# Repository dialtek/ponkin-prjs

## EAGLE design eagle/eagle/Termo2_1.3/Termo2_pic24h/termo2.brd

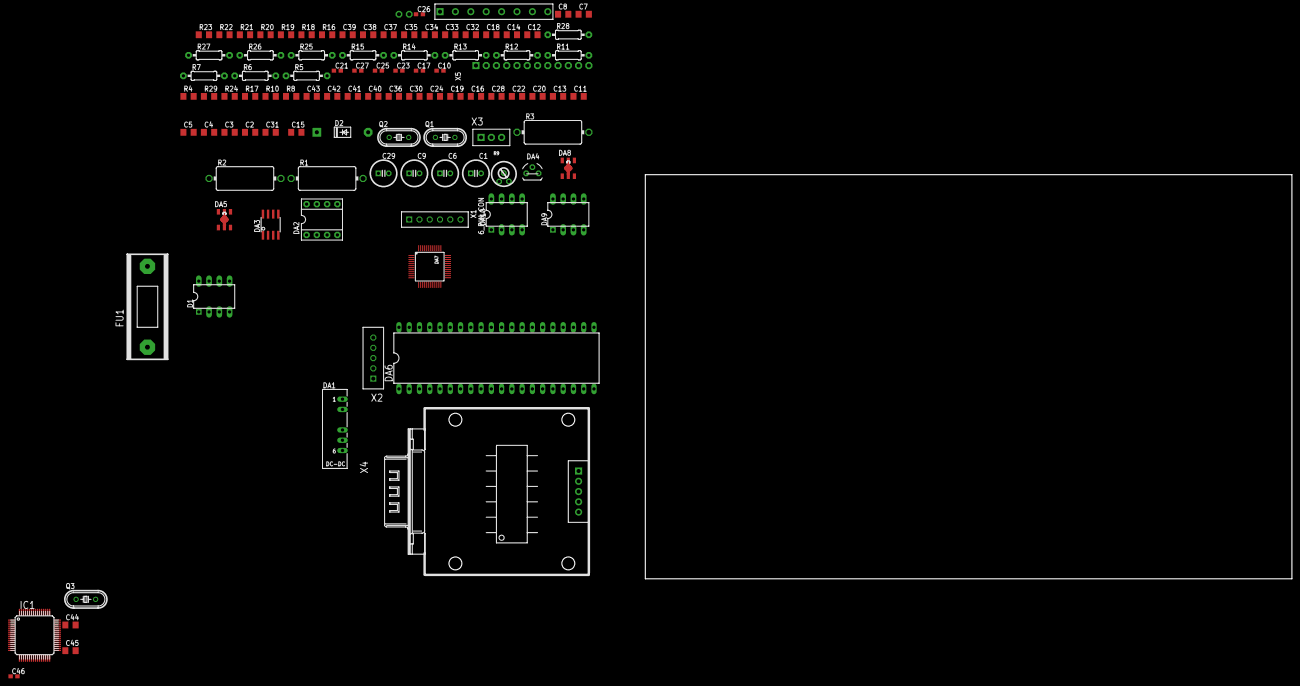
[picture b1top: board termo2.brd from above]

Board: 2 copper layers, 160.0 x 100.0 mm, 100 parts (0 on the bottom side), 77 nets, no tracks yet.

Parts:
8_PIN_: 8_PIN_CON
C1, C6, C9, C29: C100MILX6X12
C2, C3, C4, C5, C11, C13, C20, C22, C28: 0.1u; C0805D
C7, C8, C12, C14, C18, C32, C33, C34, C35, C37, C38, C39: C0805D
C10, C17, C23, C25, C27, C46: 0.1u; C0603
C15, C31: 0.01u; C0805D
C16, C30: 1u; C0805D
C19, C24, C44, C45: 12p; C0805D
C21: 1n; C0603
C26: C0603
C36: 1n; C0805D
C40, C41, C42, C43: 0.1; C0805D
D1: 6N137; DIL08
D2: 1N5061; DO41-10
DA1: NMA
DA2: INA128P; DIL08
DA3: OPA340U; SO08
DA4: DS1811; TO92-60
DA5, DA8: NJM2880; SOT89-5
DA6: PIC18F4320_40; DIL40
DA7: ADS1216ADS1216; ADS1216_PAC
DA9, DA10: CNY74-H; CNY_DIP8
FU1: FUSE5X20
IC1: PIC24HJ64GP506; TQFP64-10X10
P1, P2: 1_PIN_CON
Q1, Q2, Q3: HC49/S
R1, R2: 100k; V235/17
R3: 50k; V235/17
R4, R24: 10k; R0805D
R5, R25, R26, R27, R28: 330; 0207/10
R6, R7: 1k; 0207/10
R8, R10, R29: 22R; R0805D
R9: RTRIM3329H
R11: 100k; 0207/10
R12, R13, R14, R15: 4k7; 0207/10
R16, R18, R19, R20, R21, R22, R23: R0805D
R17: 1k; R0805D
X1: 6_PIN_CON; 6_IN_PINS
X2: PLC-5PIN
X3: PLC-3PIN
X4: KM_RS_232
X5: WINSTAR16X4_12

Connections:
!MCLR_MC: IC1.7, R4.P$1, X3.P$2
+5V: C1.PLUS, C2.1, C4.2, C5.1, C11.2, C18.2, C20.1, C22.2, C29.PLUS, C30.1, D1.7, D1.8, DA1.1, DA3.7, DA4.2, DA6.11, DA6.32, DA8.4, R4.P$2, R6.2, R9.2, R12.2, R13.2, R14.2, R15.2, X1.P$5, X2.P$2, X4.5, X5.P$2
+5V_AVDD: C10.2, C16.1, C23.2, C25.1, C26.2, C27.1, DA5.4, DA7.1, DA7.13, DA7.23, DA7.27, DA7.31
+6V: C13.2, C28.2, D2.C, DA5.1, DA5.5, DA8.1, DA8.5, FU1.P$2, R7.1
AINCOM: DA7.11, R11.1
DB4: DA6.27, X5.P$7
DB5: DA6.28, X5.P$8
DB6: DA6.29, X5.P$9
DB7: DA6.30, X5.P$10
DRDY: DA6.5, DA7.32
DSYNC: DA6.6, DA7.29
D_IN: DA7.35, R10.P$2
D_OUT: DA7.36, R8.P$2
E: DA6.19, X5.P$6
IN1.1: C36.1, C40.1, DA7.3, R17.P$1
IN1.2: C32.1, C40.2, DA7.4, R18.P$1
IN2.1: C37.1, C41.1, DA7.5, R19.P$1
IN2.2: C33.1, C41.2, DA7.6, R20.P$1
IN3.1: C38.1, C42.1, DA7.7, R23.P$1
IN3.2: C34.1, C42.2, DA7.8, R16.P$1
IN4.1: C39.1, C43.1, DA7.9, R21.P$1
IN4.2: C35.1, C43.2, DA7.10, R22.P$1
INA_OUT: DA3.3, R3.1
K2: R26.2, X1.P$2
K3: R27.1, X1.P$3
K4: R28.2, X1.P$4
KN1,PGD: DA9.7, IC1.18, R12.1, X2.P$4
KN2,PGC: DA9.6, IC1.17, R13.1, X2.P$5
KN3: DA6.38, DA10.7, R14.1
KN4: DA6.37, DA10.6, R15.1
MCLR: X2.P$1, X3.P$1
unnamed: C19.2, DA6.13, Q2.1
unnamed: C24.2, DA6.14, Q2.2
unnamed: DA9.4, R26.1
unnamed: C31.1, DA8.3
unnamed: D1.6, DA6.35, R6.1
unnamed: DA6.18, R29.P$2
unnamed: C21.2, DA7.14
unnamed: DA4.1, X3.P$3
unnamed: DA6.24, R10.P$1
unnamed: C14.2, DA7.25, Q1.2
unnamed: C12.2, DA7.26, Q1.1
unnamed: DA6.23, R8.P$1
unnamed: 8_PIN_.P$6, R16.P$2
unnamed: 8_PIN_.P$1, R17.P$2
unnamed: 8_PIN_.P$2, R18.P$2
unnamed: 8_PIN_.P$7, R21.P$2
unnamed: DA10.1, R27.2
unnamed: 8_PIN_.P$8, R22.P$2, R24.P$1
unnamed: DA10.4, R28.1
unnamed: R7.2, X5.P$11
unnamed: 8_PIN_.P$5, R23.P$2
unnamed: C6.PLUS, C8.1, DA1.6, DA2.7
unnamed: 8_PIN_.P$3, R19.P$2
unnamed: 8_PIN_.P$4, R20.P$2
unnamed: DA2.5, DA3.2, DA3.6
unnamed: DA2.6, R1.2
unnamed: C7.1, C9.MINUS, DA1.4, DA2.4
unnamed: R1.1, R2.2
unnamed: R2.1, R3.2
unnamed: C15.1, DA5.3
unnamed: D1.2, R5.1
unnamed: D1.3, P1.P$1
unnamed: P2.P$1, R5.2
OSC1: C44.2, IC1.39, Q3.1
OSC2: C45.2, IC1.40, Q3.2
PE: C1.MINUS, C2.2, C3.2, C4.1, C5.2, C6.MINUS, C7.2, C8.2, C9.PLUS, C10.1, C11.1, C12.1, C13.1, C14.1, C15.2, C16.2, C17.2, C18.1, C19.1, C20.2, C21.1, C22.1, C23.1, C24.1, C25.2, C26.1, C27.2, C28.1, C29.MINUS, C30.2, C31.2, C32.2, C33.2, C34.2, C35.2, C36.2, C37.2, C38.2, C39.2, C44.1, C45.1, C46.1, C46.2, D1.5, D2.A, DA1.2, DA1.5, DA2.2, DA3.4, DA4.3, DA5.2, DA5.21, DA6.12, DA6.31, DA7.2, DA7.12, DA7.18, DA7.19, DA7.20, DA7.21, DA7.22, DA7.28, DA7.30, DA7.45, DA7.48, DA8.2, DA8.21, DA9.2, DA9.3, DA9.5, DA9.8, DA10.2, DA10.3, DA10.5, DA10.8, IC1.38, IC1.41, R9.1, R11.2, R24.P$2, X1.P$6, X2.P$3, X4.1, X5.P$1, X5.P$12
R15: DA9.1, R25.2
REF: C3.1, C17.1, DA2.3, DA7.46, DA7.47
RESET: DA6.7, DA7.24
RS: DA6.21, X5.P$4
RW: DA6.22, X5.P$5
SCLK: DA7.34, R29.P$1
TX_EN: DA6.20, X4.4
V0CON: R9.3, X5.P$3
VDD: FU1.P$1, IC1.10, IC1.26, IC1.57
VSS: IC1.9, IC1.25

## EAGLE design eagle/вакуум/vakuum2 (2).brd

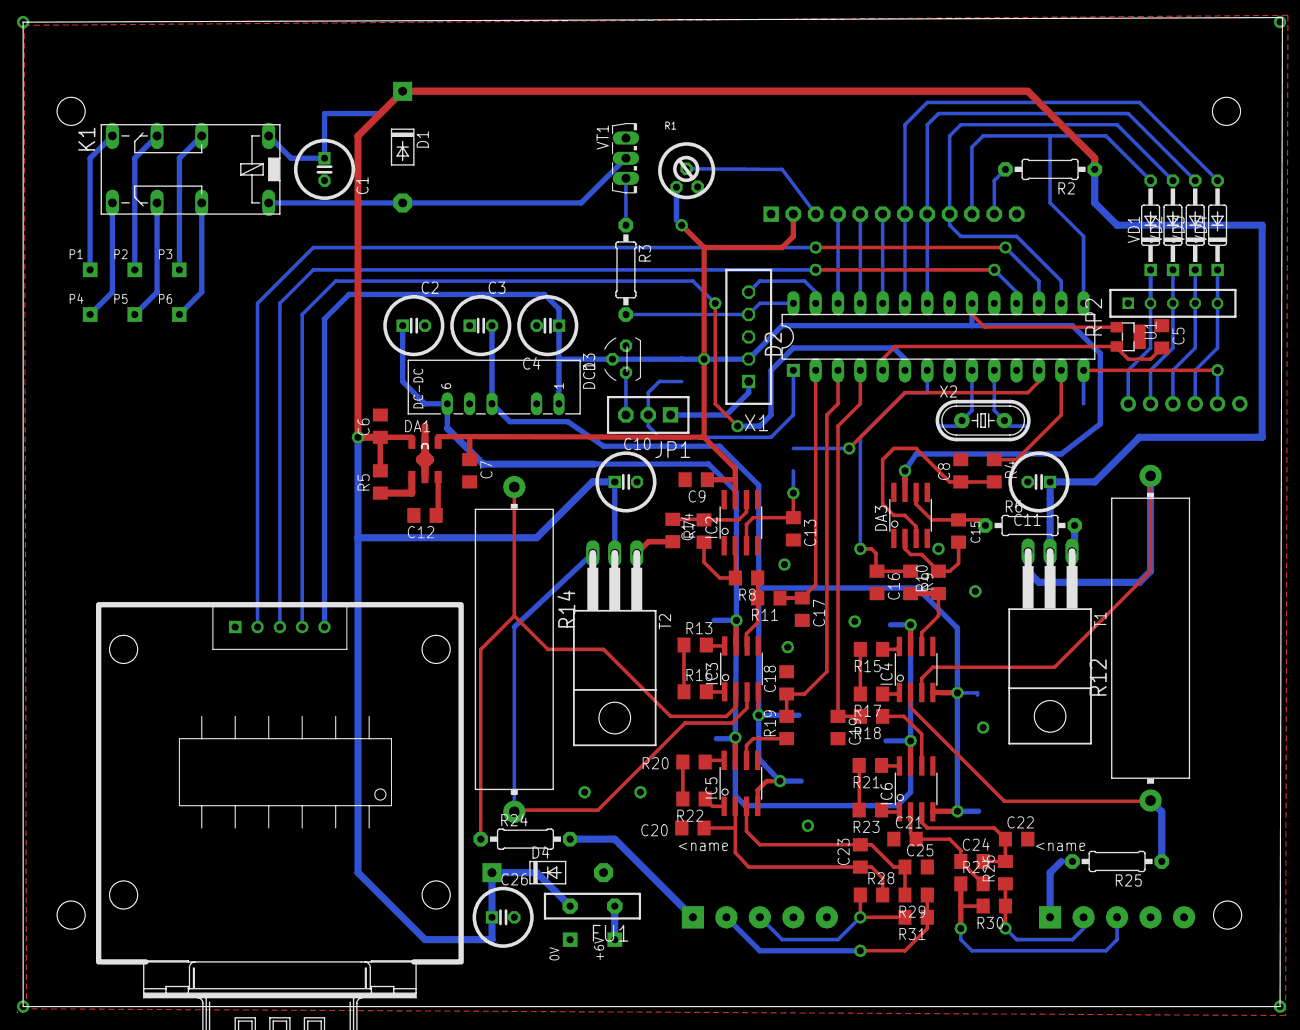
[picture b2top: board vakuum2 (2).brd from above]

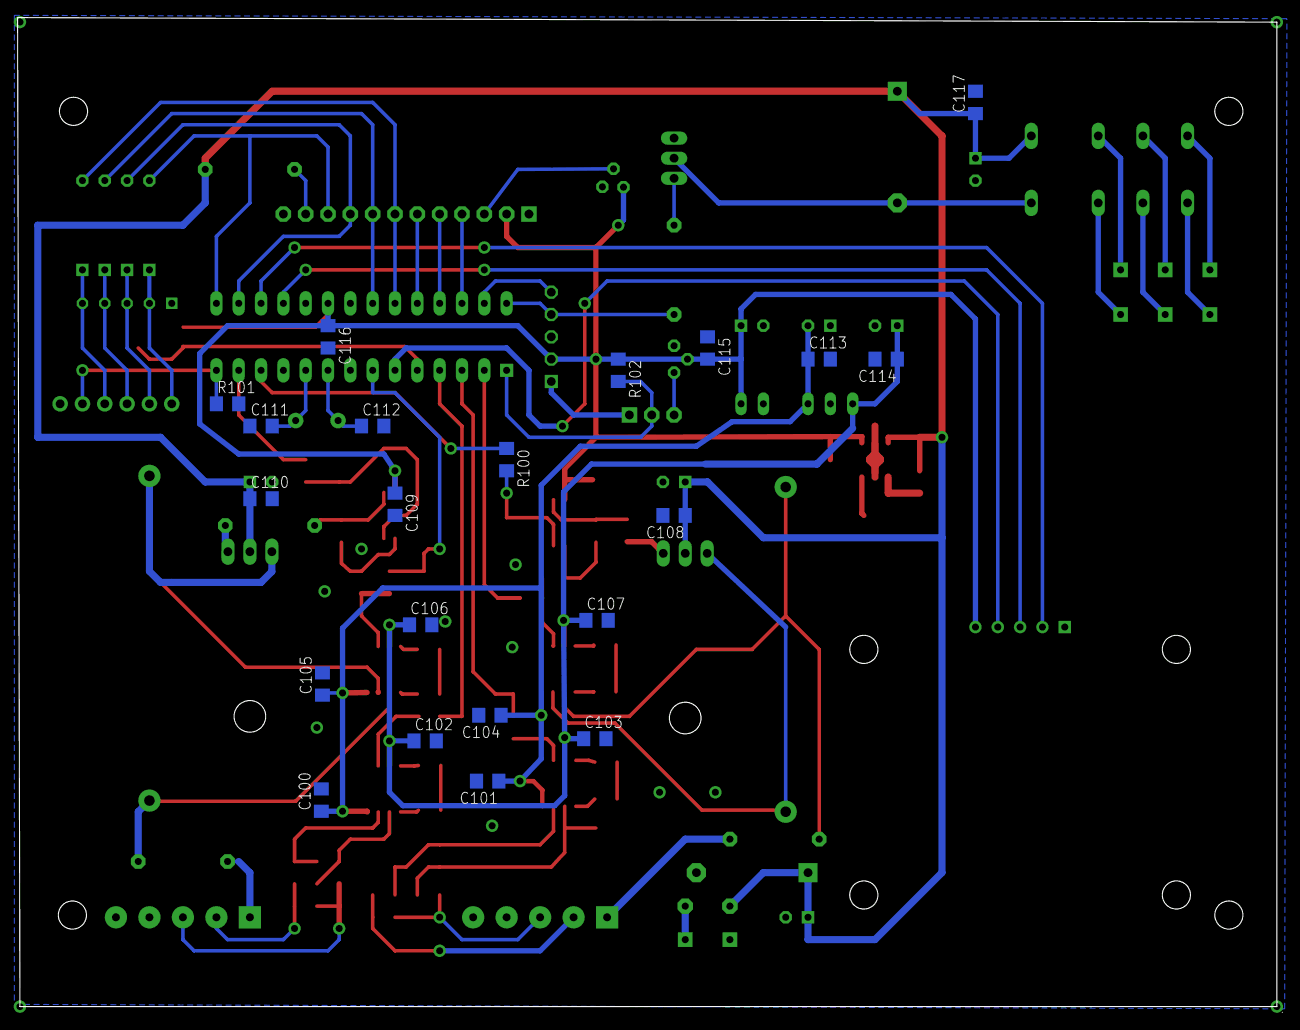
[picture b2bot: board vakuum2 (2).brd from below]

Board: 2 copper layers, 143.9 x 113.2 mm, 116 parts (21 on the bottom side), 85 nets.

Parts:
0V: PIN1
+6V: PIN1
C1, C2, C3, C4, C10, C11, C26: C100MILX6X12
C5, C9, C106: C0805D
C6, C20, C21, C22, C25, C100, C101, C102, C103, C104, C105, C107, C108, C109, C110, C113, C114, C115, C116, C117: 0.1; C0805D
C7: 1u; C0805D
C8, C13, C16, C17, C18, C19: 10uF; C0805D
C12: 10n; C0805D
C14, C15: 47n; C0805D
C23, C24: 2.2; C0805D
C111, C112: 16pf; C0805D
D1, D4: 1N5061; DO41-10
D2: PIC18F2320DIP; DIL28-3
D3: DS1811; TO92-60
DA1: NJM2880; SOT89-5
DA3: OPA340U; SO08
DC1: NMA
FU1: RA90
IC2: OPA340U; SO08
IC3, IC4, IC5, IC6: INA129U; SO08
JP1: JP3PIN; PLC-3PIN
K1: 351
P1, P2, P3, P4, P5, P6: PIN1
R1: 15K; RTRIM3329H
R2: 0207/10
R3, R6: 1k; 0207/10
R4, R100, R102: 10K; R0805D
R5: 300k; R0805D
R7: 1k; R0805D
R8, R10: 5.1k; R0805D
R9, R11, R18, R19: 1K; R0805D
R12, R14: HPS932
R13, R15, R16, R17: 1K 1%; R0805D
R20, R21: 30 1%; R0805D
R22, R23: 100 1%; R0805D
R24, R25: 12E; 0207/10
R26, R27, R28, R29: 300; R0805D
R30, R31: 100k; R0805D
R101: 10k; R0805D
RP2: SIP5
T1, T2: KT829; T-30
U1: REF3140; SOT23-W
VD1, VD2, VD3, VD4: KD521; DO35-10
VT1: KT815; TO126V
WINSTAR_DISP1: WINSTAR16X4_12
X1: PIC_ISP_CONN; PLC-5PIN
X2: 10 Mhz; HC49/S
X3: KM_RS_232
X4, X5: MB332-381

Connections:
0V: 0V.P$1, C1.MINUS, C2.MINUS, C3.PLUS, C4.MINUS, C5.1, C6.2, C7.2, C8.2, C9.2, C10.MINUS, C11.MINUS, C12.2, C13.2, C16.2, C17.2, C18.2, C19.2, C20.1, C21.1, C22.2, C25.2, C26.MINUS, C100.2, C101.2, C102.2, C103.2, C104.2, C105.2, C106.2, C107.2, C108.2, C109.2, C110.2, C111.1, C112.2, C113.2, C114.2, C115.1, C116.2, C117.2, D2.8, D2.19, D3.3, D4.A, DA1.2, DA1.21, DA3.4, DC1.2, DC1.5, IC2.4, IC3.5, IC4.5, IC5.5, IC6.5, R1.2, R101.P$2, RP2.1, U1.GND, VT1.1, WINSTAR_DISP1.P$1, WINSTAR_DISP1.P$12, X1.P$3, X3.1, X4.4, X4.5, X5.4, X5.5
+5V: C4.PLUS, C7.1, C9.1, C109.1, C115.2, C116.1, D2.20, D3.2, DA1.4, DA3.7, DC1.1, IC2.7, R1.1, R102.P$1, U1.IN, WINSTAR_DISP1.P$2, X1.P$2, X3.5
+6V: C1.PLUS, C6.1, C10.PLUS, C11.PLUS, C26.PLUS, C108.1, C110.1, C117.1, D1.C, D4.C, DA1.5, FU1.P$2, K1.1, R2.1, R5.P$2, T1.2, T2.2
+15V: C2.PLUS, C102.1, C103.1, C106.1, C107.1, C114.1, DC1.6, IC3.7, IC4.7, IC5.7, IC6.7
-15V: C3.MINUS, C100.1, C101.1, C104.1, C105.1, C113.1, DC1.4, IC3.4, IC4.4, IC5.4, IC6.4
AN0: C17.1, D2.2, R11.P$1
AN1: C18.1, D2.3, R19.P$2
AN2: C19.1, D2.4, R18.P$2
AN4: C16.1, D2.7, R9.P$1
CCP1: D2.13, R4.P$1
CCP2: D2.12, R100.P$1
EN: D2.6, X3.4
MCLR: JP1.P$1, X1.P$1
unnamed: IC5.6, R19.P$1
unnamed: C112.1, D2.9, X2.1
unnamed: C23.2, C25.1, IC5.3, R29.P$2
unnamed: C111.2, D2.10, X2.2
unnamed: R20.P$2, R22.P$2
unnamed: IC5.1, R22.P$1
unnamed: D2.1, JP1.P$2, R102.P$2
unnamed: C21.2, C24.1, IC6.2, R27.P$2
unnamed: IC6.8, R21.P$1
unnamed: IC6.1, R23.P$1
unnamed: C22.1, C24.2, IC6.3, R26.P$2
unnamed: IC4.8, R15.P$1
unnamed: IC6.6, R18.P$1
unnamed: R15.P$2, R17.P$2
unnamed: R13.P$1, R16.P$1
unnamed: IC5.8, R20.P$1
unnamed: R21.P$2, R23.P$2
unnamed: C20.2, C23.1, IC5.2, R28.P$2
unnamed: R2.2, WINSTAR_DISP1.P$11
unnamed: C15.1, DA3.2, R10.P$2
unnamed: +6V.P$1, FU1.P$1
unnamed: IC3.6, R8.P$1, R11.P$2
unnamed: D3.1, JP1.P$3
unnamed: R1.3, WINSTAR_DISP1.P$3
unnamed: C14.2, IC2.6, R7.P$1
unnamed: C13.1, IC2.3, R100.P$2
unnamed: R7.P$2, T2.1
unnamed: IC3.8, R13.P$2
unnamed: IC3.1, R16.P$2
unnamed: IC3.3, R14.2, T2.3
unnamed: IC3.2, R14.1, R24.1
unnamed: D1.A, K1.16, VT1.2
unnamed: IC4.6, R9.P$2, R10.P$1
unnamed: C14.1, IC2.2, R8.P$2
unnamed: K1.S2, P4.P$1
unnamed: C15.2, DA3.6, R6.1
unnamed: C8.1, DA3.3, R4.P$2
unnamed: R6.2, T1.1
unnamed: R3.1, VT1.3
unnamed: IC4.1, R17.P$1
unnamed: IC4.3, R12.2, T1.3
unnamed: IC4.2, R12.1, R25.1
unnamed: DA1.1, R5.P$1
unnamed: C12.1, DA1.3
unnamed: K1.O2, P5.P$1
unnamed: K1.S1, P1.P$1
unnamed: K1.O1, P2.P$1
unnamed: K1.P1, P3.P$1
unnamed: K1.P2, P6.P$1
PGC: D2.27, X1.P$5
PGD: D2.28, R3.2, X1.P$4
RB1: D2.22, VD3.A, WINSTAR_DISP1.P$8
RB2: D2.23, VD4.A, WINSTAR_DISP1.P$7
RB3: D2.24, WINSTAR_DISP1.P$6
RB4: D2.25, WINSTAR_DISP1.P$5
RB5: D2.26, WINSTAR_DISP1.P$4
RC3: D2.14, R101.P$1
RC4: D2.15, VD1.A, WINSTAR_DISP1.P$10
RC5: D2.16, VD2.A, WINSTAR_DISP1.P$9
REF: C5.2, D2.5, U1.OUT
RX: D2.18, X3.3
SENS1.1: R24.2, X4.1
SENS1.2: R29.P$1, R31.P$1, X4.2
SENS1.3: R28.P$1, R31.P$2, X4.3
SENS2.1: R25.2, X5.1
SENS2.2: R26.P$1, R30.P$1, X5.2
SENS2.3: R27.P$1, R30.P$2, X5.3
SW1: RP2.2, VD1.C
SW2: RP2.3, VD2.C
SW3: RP2.4, VD3.C
SW4: RP2.5, VD4.C
TX: D2.17, X3.2
